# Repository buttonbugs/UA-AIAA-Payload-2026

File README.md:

# UA AIAA Payload 2026

This repository includes the payload codes for the [UA AIAA](https://uaaiaa.org/) Rocket Competition Team.

## Preview

### Rocket Launch Data

See YouTube video: https://www.youtube.com/watch?v=IQ9gblNF-8s&list=PLdFZmiWGbxr0

https://github.com/user-attachments/assets/e6d3bb94-cc8a-4640-be77-5c40b0f65d72

### Rocket Prelaunch Testing

#### Pressure and Temperature

#### Magnetic Field

#### Acceleration

## Software

**VS Code Extension:** [PlatformIO IDE](https://marketplace.visualstudio.com/items?itemName=platformio.platformio-ide)

**Framework:** Arduino

### Libraries

| Libraries             | Installation                  |
| -                     | -                             |
| DFRobot_OzoneSensor   | [DFRobot Website](https://wiki.dfrobot.com/Gravity_IIC_Ozone_Sensor_(0-10ppm)%20SKU_SEN0321) |
| ICM_20948             | PlatformIO &rarr; Libraries   |
| Adafruit_BME280       | PlatformIO &rarr; Libraries   |
| SD                    | PlatformIO &rarr; Libraries   |
| Adafruit_SGP40        | PlatformIO &rarr; Libraries   |
| WatchDog              | [Arduino Built-In Library](https://docs.arduino.cc/libraries/watchdog/) |

## Hardware

### Pin Configuration

**Pin Configuration for I²C and SPI**

| Pin Name | Pin No.| Protocol |
| - | - | - |
| SDA | A4 | I²C |
| SCL | A5 | I²C |
| CLK / SCK | D13 | SPI |
| DO / MISO | D12 | SPI |
| DI / MOSI | D11 | SPI |
| CS for the SD Card Reader | D10 (or any) | SPI |

**Pin Configuration for Ultrasonic Sensor**

| Sensor | Trigger Pin | Echo Pin |
| - | - | - |
| Ultrasonic Sensor 1 | D2 | D3 |
| Ultrasonic Sensor 2 | D4 | D5 |
| Ultrasonic Sensor 3 | D6 | D7 |

**Other Pin Configuration**

| Sensor | Signal Pin |
| - | - |
| SW-18010P 1 (Horizontal)  | A6 |
| SW-18010P 2 (Vertical)    | A7 |

Reference: [Arduino Nano Every Full Pinout Diagram (Official)](https://content.arduino.cc/assets/Pinout-NANOevery_latest.pdf)

### Electronics

| Electronics | Description | Voltage | Protocol | On PCB |
| - | - | - | - | - |
| Microcontroller | [Arduino Nano Every](https://store-usa.arduino.cc/products/nano-every) | 5V | - | Y |
| SD Card Reader | [Adafruit MicroSD Card Breakout ADA254](https://www.amazon.com/Adafruit-MicroSD-Breakout-Board-ADA254/dp/B00NAY2NAI/) | 5V | SPI | Y |
| Ozone Sensor | [DFRobot Gravity: IIC Ozone Sensor V1.0](https://wiki.dfrobot.com/Gravity_IIC_Ozone_Sensor_(0-10ppm)%20SKU_SEN0321) | 3.3V - 5.5V | I²C | N |
| VOC Sensor | [Waveshare SGP40 VOC Sensor](https://www.waveshare.com/wiki/SGP40_VOC_Sensor#Test_the_codes) | 3.3V or 5V | I²C | N |
| IMU Sensor | [SparkFun 9DoF IMU Breakout - ICM 20948](https://www.amazon.com/SparkFun-Breakout-ICM-20948-connection-Accelerometer-Magnetometer/dp/B07VNV3WKL/) | 1.95 V - 3.6 V | I²C | Y |
| BME280 Sensor | [Starry GY-BME280 5V](https://www.amazon.com/Starry-Atmospheric-Pressure-Temperature-GY-BME280/dp/B0DRCNNBF3/) | 5V | I²C | Y |
| Ultrasonic Sensor | HC-SR04 | 5V | - | N |
| Vibration Sensor | [SW-18020P](https://www.adafruit.com/product/2384) | &le; 12V | - | N |

## PCB

### PCB resources

Arduino footprints and symbols: [Alarm-Siren/arduino-kicad-library](https://github.com/Alarm-Siren/arduino-kicad-library)

PCB manufacturer: [JLCPCB](https://jlcpcb.com/)

### How to generate Gerber and Drill files in KiCAD 9

See https://jlcpcb.com/help/article/how-to-generate-gerber-and-drill-files-in-kicad-9

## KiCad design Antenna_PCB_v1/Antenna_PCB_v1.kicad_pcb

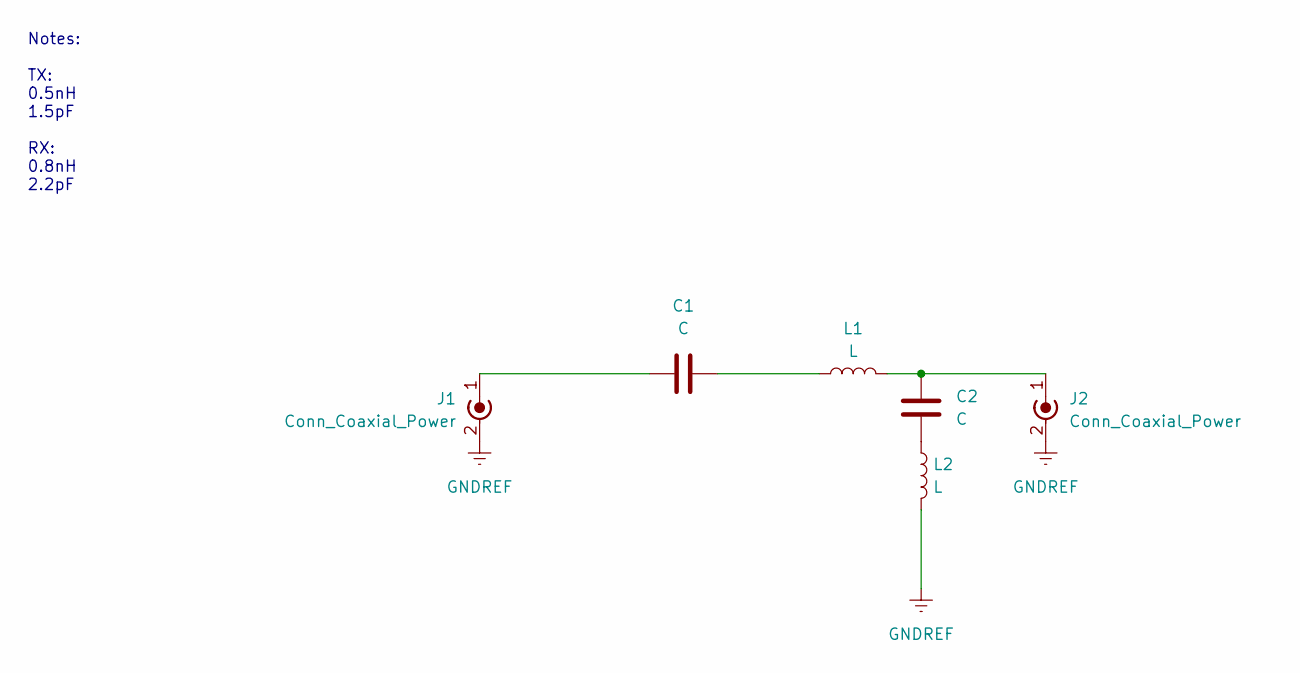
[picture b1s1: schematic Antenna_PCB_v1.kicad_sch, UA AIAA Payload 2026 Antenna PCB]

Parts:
C1, C2: C; C_0402_1005Metric
J1, J2: Conn_Coaxial_Power; SMA_Molex_73251-1153_EdgeMount_Horizontal
L1, L2: L; L_0402_1005Metric

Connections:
GNDREF: J1.2 (Ext), J2.2 (Ext), L2.2
unnamed: C1.2, L1.1
unnamed: C2.2, L2.1
unnamed: C1.1, J1.1 (In)
unnamed: C2.1, J2.1 (In), L1.2

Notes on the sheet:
Notes: TX: 0.5nH 1.5pF RX: 0.8nH 2.2pF

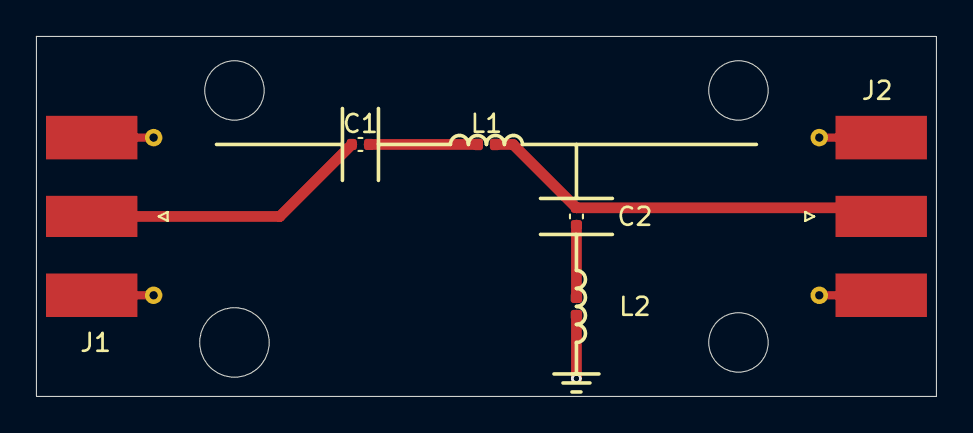
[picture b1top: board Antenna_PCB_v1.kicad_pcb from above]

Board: 2 copper layers, 50.0 x 20.0 mm, 6 parts (0 on the bottom side), 5 nets.

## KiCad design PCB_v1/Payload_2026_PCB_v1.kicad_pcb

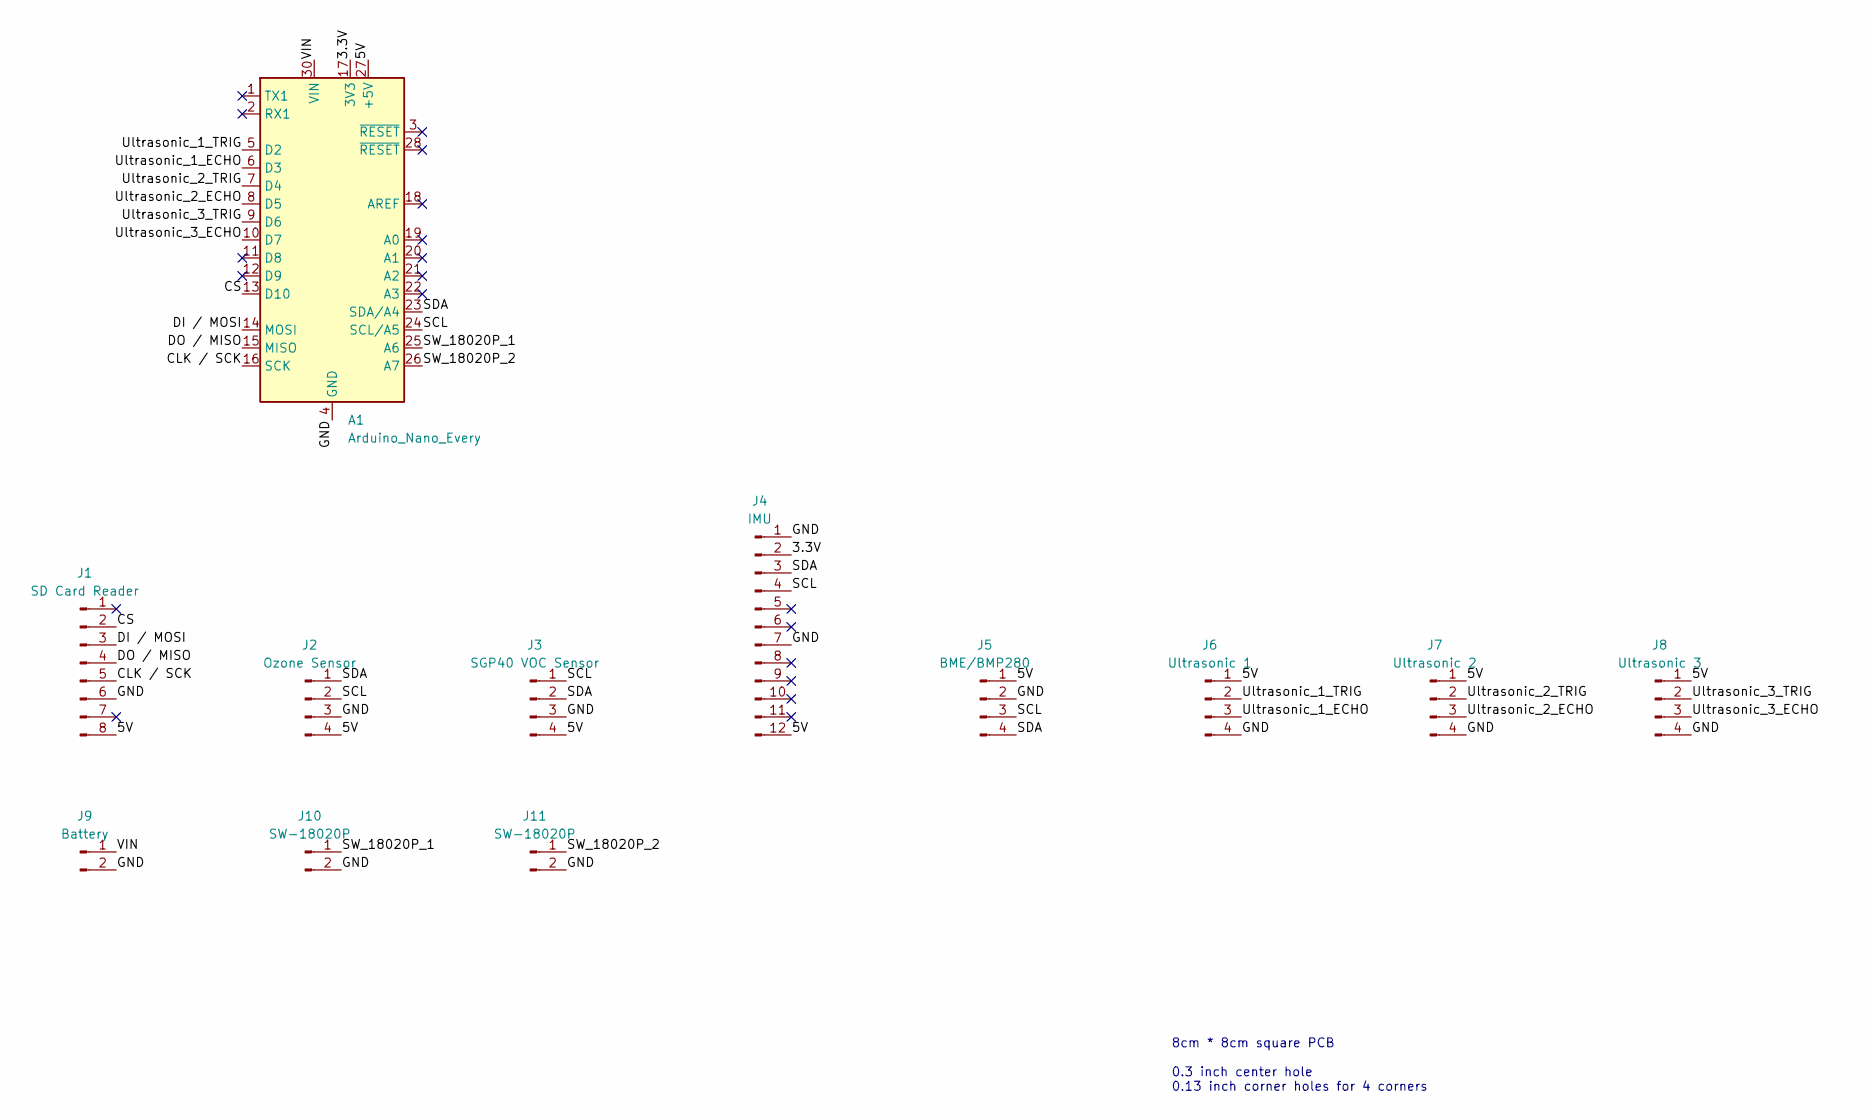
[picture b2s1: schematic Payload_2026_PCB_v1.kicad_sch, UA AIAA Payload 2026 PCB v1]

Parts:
A1: Arduino_Nano_Every; Arduino_Nano
J1: SD Card Reader; SD_Card_Reader
J2: Ozone Sensor; Conn_01x04_Pin
J3: SGP40 VOC Sensor; Conn_01x04_Pin
J4: IMU
J5: BME/BMP280; BME280_Sensor
J6: Ultrasonic 1; Conn_01x04_Pin
J7: Ultrasonic 2; Conn_01x04_Pin
J8: Ultrasonic 3; Conn_01x04_Pin
J9: Battery
J10, J11: SW-18020P; SW_18020P

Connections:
/3.3V: A1.17 (3V3), J4.2
/5V: A1.27 (+5V), J1.8, J2.4, J3.4, J4.12, J5.1, J6.1, J7.1, J8.1
/CLK / SCK: A1.16 (SCK), J1.5
/CS: A1.13 (D10), J1.2
/DI / MOSI: A1.14 (MOSI), J1.3
/DO / MISO: A1.15 (MISO), J1.4
/GND: A1.4 (GND), A1.29 (GND), J1.6, J2.3, J3.3, J4.1, J4.7, J5.2, J6.4, J7.4, J8.4, J9.2, J10.2, J11.2
/SCL: A1.24 (SCL/A5), J2.2, J3.1, J4.4, J5.3
/SDA: A1.23 (SDA/A4), J2.1, J3.2, J4.3, J5.4
/SW_18020P_1: A1.25 (A6), J10.1
/SW_18020P_2: A1.26 (A7), J11.1
/Ultrasonic_1_ECHO: A1.6 (D3), J6.3
/Ultrasonic_1_TRIG: A1.5 (D2), J6.2
/Ultrasonic_2_ECHO: A1.8 (D5), J7.3
/Ultrasonic_2_TRIG: A1.7 (D4), J7.2
/Ultrasonic_3_ECHO: A1.10 (D7), J8.3
/Ultrasonic_3_TRIG: A1.9 (D6), J8.2
/VIN: A1.30 (VIN), J9.1

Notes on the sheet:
8cm * 8cm square PCB 0.3 inch center hole 0.13 inch corner holes for 4 corners

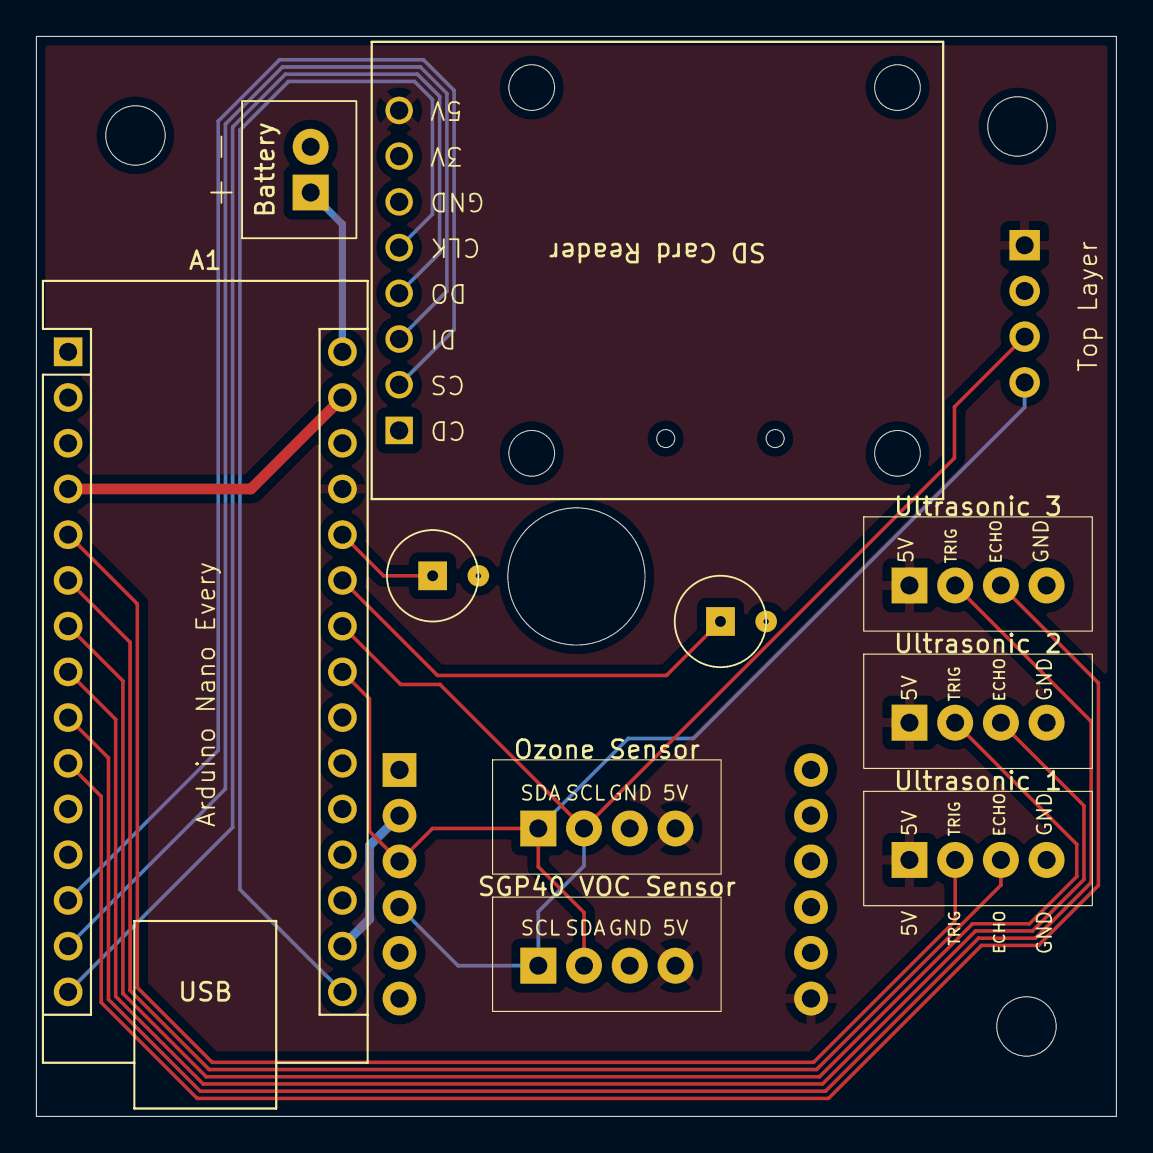
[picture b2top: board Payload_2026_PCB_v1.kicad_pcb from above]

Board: 2 copper layers, 60.0 x 60.0 mm, 12 parts (0 on the bottom side), 18 nets.

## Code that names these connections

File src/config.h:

#ifndef CONFIG
#define CONFIG

#define FILE_SIZE_LIMIT 4E9             // bytes, create another data file when the current file size exceeds the this number; 4GB = 4,294,967,296 bytes > 4E9 bytes

#define SAMPLE_ECHOTERVAL 10            // milliseconds per data sample

#define ULTRASONIC_TIMEOUT_US 30000     // microseconds, prevent the code from freezing when unable to get data from the ultrasonic sensor

#define VIBRATION_TIMEOUT_MS 1000       // milliseconds, the vibration period will be set to 0 if no vibration is detected within the timeout

#define E_DECIMAL_PLACE 7               // Scientific notation decimal places, Arduino float data types typically provide 6 to 7 decimal digits of precision

/* Pin Configuration */
// Ultrasonic Sensor
#define ULTRASONIC_1_TRIG 2
#define ULTRASONIC_1_ECHO 3
#define ULTRASONIC_2_TRIG 4
#define ULTRASONIC_2_ECHO 5
#define ULTRASONIC_3_TRIG 6
#define ULTRASONIC_3_ECHO 7

// Vibration Sensor
#define VIBRATION_SENSOR_1 A6
#define VIBRATION_SENSOR_2 A7

// SD Card Reader
#define SD_CARD_CS 10               // SD card Chip Select (set to 10 by default)

#endif

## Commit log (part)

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2026-02-15 Create pio project
2026-02-15 Import "DFRobot_OzoneSensor.h" and test the ozone sensor
2026-02-15 sgp40 voc sensor test
2026-02-15 Update README.md Sensor List
2026-02-15 Nothing
2026-02-22 Sensor tests finished
2026-02-22 SD Card Test; Update README.md
2026-02-23 Finish ultrasonic sensor codes
2026-02-23 SC card codes for scv column headers
2026-02-23 Change the function sequence in write_sd.cpp
2026-02-23 write_sd.cpp char->string fix
2026-02-23 Codes for data wrting finished
2026-02-23 SD Card Writing Test (Failed at write_sd.cpp line 120 column 30); there might be something wrong with the wiring of IMU
2026-03-01 Fix SD card writing issue
2026-03-01 Fix voc and initial column headers
2026-03-02 Create PCB_v1; import Arduino symbols
2026-03-02 PCB Footprints finished
2026-03-02 Finish PCB Design
2026-03-02 Write DOTO List in sch
2026-03-02 Update PCB layout
2026-03-02 Update PCB Silkscreen Labels
2026-03-03 Add UA AIAA Logo onto PCB
2026-03-03 Set the VIN thickness on PCB
2026-03-03 Add SW-18020P to the PCB; generate gerber files
2026-03-03 Update PCB 3D Model
2026-03-03 Add Library Instructions and TODO List
2026-03-03 Fix arrows in README.md
2026-03-04 Fix url typo in README.md
2026-03-04 Fix a typo in README.md
2026-03-22 Generate Gerber files
2026-03-22 Finish ultrasonic code
2026-03-22 Update Gerber files
2026-03-22 Add another vibration sensor
2026-03-22 Finish vibration sensor code
2026-03-22 Add vibration sensor timeout
2026-03-22 End testing
2026-03-22 Fix PCB isolated GND caused by new vibration sensor holes
2026-04-13 Add sensor initialization debugging
2026-04-19 Specify upload port
2026-04-19 Increase single file size to less than 4GB
2026-04-19 Create Antenna PCB
2026-04-19 Add holes to PCB
2026-04-20 Upload data sample
2026-04-21 Fix antenna PCB circuit
2026-04-21 Update gerber files and 3D model
2026-04-26 Add KiCad temp files to gitignore
2026-04-26 Update antenna PCB 3D model
2026-06-14 Remove TODO
2026-06-15 Drawing basic lines
2026-06-15 Rename
2026-06-19 Organize testing data
2026-06-19 Add macOS USB drive system hidden folders to .gitignore
2026-06-19 Upload 20260617142200CDT testing data
2026-06-19 Add payload starting time to config file
2026-06-19 Add data combining and filtering code
2026-06-19 Rename "data_filter.py" to "data_read.py"
2026-06-19 Add abs data calculation
2026-06-19 Finish acceleration graph rendering
2026-06-19 Convert list to np.array when reading data from file
2026-06-19 Draw simple graphs
2026-06-19 Rename "data_processing.py" to "data_plot.py"
2026-06-19 Change combined and filtered data file names and locations
2026-06-19 Draw temperature and save plot to files
2026-06-19 Specify labels for temperature graph
2026-06-19 Fix variable naming error
2026-06-19 Swap BME280 temperature and IMU temperature
2026-06-19 Draw pressure and temperature dual-axis chart
2026-06-19 Define grid style using using alpha instead of linewidth
2026-06-19 Upload air density formulas provided by Google AI
2026-06-19 Add Buck equation given temperature in celsius
2026-06-19 Fix ultrasonic data naming error
2026-06-19 Finish air density calculation code
2026-06-19 Draw air density graph
2026-06-19 Remove legend from density graph
2026-06-19 Remove unnecessary whitespace
2026-06-20 Change figure size
2026-06-20 Change acceleration legends
2026-06-20 Draw graph for magnetic field
2026-06-21 Upload payload data
2026-06-21 Upload camera system gcsv data
2026-06-21 Upload GPS data
2026-06-21 Add mp4 files to .gitattributes
2026-06-21 Upload rocket camera recording
2026-06-21 Draw payload graph
2026-06-21 Set y limit to pressure graph
2026-06-21 Rotate 45 deg for axis in pressure_temp graph
